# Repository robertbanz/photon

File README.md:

# Photon Game Platform

This is a software (and hardware) suite to run the Photon game system on reasonably modern hardware.

The software is known to run on FreeBSD, though there is nothing that would stop it from running cleanly on any modern Unix with the appropriate dependencies installed. While previous revisions involved some C modules, everything now is just raw Tcl/Tk.

TL;DR Check this out in /usr/photon, and you're good to go. (will get to the specifics later)

system_build/game contains some instructions that were used to build the "game computer" we have used at PhoCon. This consists of a Mac-based host (that runs the lighting control software natively), and two virtual machines. One that runs pfsense and acts as a router to the private network that runs the Photon bits, and a second VM that runs the game software.

## Hardware

Previous revisions of this software -- you can check back in the commit history -- were expected to run on PC hardware (a Pentium at the time) on FreeBSD 2.x. It used a kernel module that modified the low-level timer handling to match what the Photon player units (PODs) expect. (see the README in the photon_gamma repository for more of that story)

As PC environment has evolved, the ability to match the Photon timing requirements became difficult. As part of making sure the software could move on and work on platforms beyond that could be picked up at computer swap-meets, some hardware assistance was required. The first attempt was to use some Arduino hardware, but a bare Arduino was not capable of reliably matching the POD's timing. I developed what I called the "PhoBoard" (schematics and layout in Eagle format are under hardware/) that provides an accurate timing interrupt in addition to an RS232-level serial port to connect to the central radio, and a modulated IR output when using the game computer itself as the entry terminal for the PODs.

The firmware for the PhoBoard(tm) is located in src/platformio/radio_interface. It is expected to run on an Arduino DUE, and be connected to the game computer (or game computer VM) via its programming port.

## Software

There are four primary components to the software. You'll find a lot of support scripts sitting around in bin/ to manage them, but this is what's important.

*  *bin/main* - It's called main for a reason. Listens on some ports for the ET & Displays to talk to, talks to the central radio via the Arduino, plays the game soundtrack, and has some fun menus to play with.
*  *bin/et* - The entry terminal. Talks to "main" to control game state. Can either use the IR emitter that *main* controls via the Arduino, or, to something connected to a local serial port that can provide a modulated IR output.
*  *bin/{cg,pg}display* - These drive the "Current Game" display, or "Post Game" display. At PhoCon we've ran these on Intel ComputeSticks running Ubuntu. They just need to be able to connect to the game computer and database to do their thing. They get constant updates about the state of the game, and in the case of the current game display, information about player state changes from *main* as they happen.  These have an "-hd" argument that selects for the 1080p layout, vs the old NTSC resolution screen layouts. (at PhoCon, all the displays are "hd")
*  *database* - The PostgreSQL database handles all of the state. For example, when the ET stages a game, it writes the data there, and just tells *main* to "start game number x". Similarly, when the displays need information about the game (or previous game), they query the DB.

### Running It In Production

*  The scripts that drive the ET & displays run them in a loop that upon startup will try to 'rsync' the entire /usr/photon tree from the game computer so they're running the latest revision of code.

*  As we're typically running this in a VM, if you've set up the FreeBSD image as I have, it launches the X windows server in a virtual frame buffer that's available via a VNC connection.

*  It also sets up PulseAudio (dot dot dot Total Junk dot dot dot SO much latency. So bad) to serve up the default audio input as the "background music" for the game, which will be faded out when the game starts.

## Configuration

etc/game.conf and etc/game.conf.local specify site specific and machine specific (respectively) parameters for system functionality. For example, the game.conf.local will specify a serial tty for the ET's IR output, while game.conf.local on the game computer points to the IR on the PhoBoard. game.conf is synced during the 'rsync' mentioed above, but .local is excluded.

## Having Fun

### Game Modes

The game modes available are defined in the database table g_modes, and make reference to actual code in lib/modes which define how various game events are handled. All current game modes use 'standard' but twiddle various parameters, but it's possible to change all the behaviors you want.

### Game Soundtracks

Similar to the game modes, the soundtracks and their lengths, etc, are defined in the g_tracks database table.

### Display Defaults

In lib/, the \*.defaults files -- in X Resources format -- allow tweaking of various fonts and layout parameters. The cg_idle sub directories contain custom tasks to display in-beween games. Perfect for advertising.

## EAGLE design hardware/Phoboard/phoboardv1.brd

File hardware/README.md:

#Hardware Designs

## Phoboard

Arduino shield to interface with the old Photon radio. (Designed to work on an
Arduino Due, 3.3v). Used in conjunction with the game software and the firmware
in src/platformio/radio_interface.

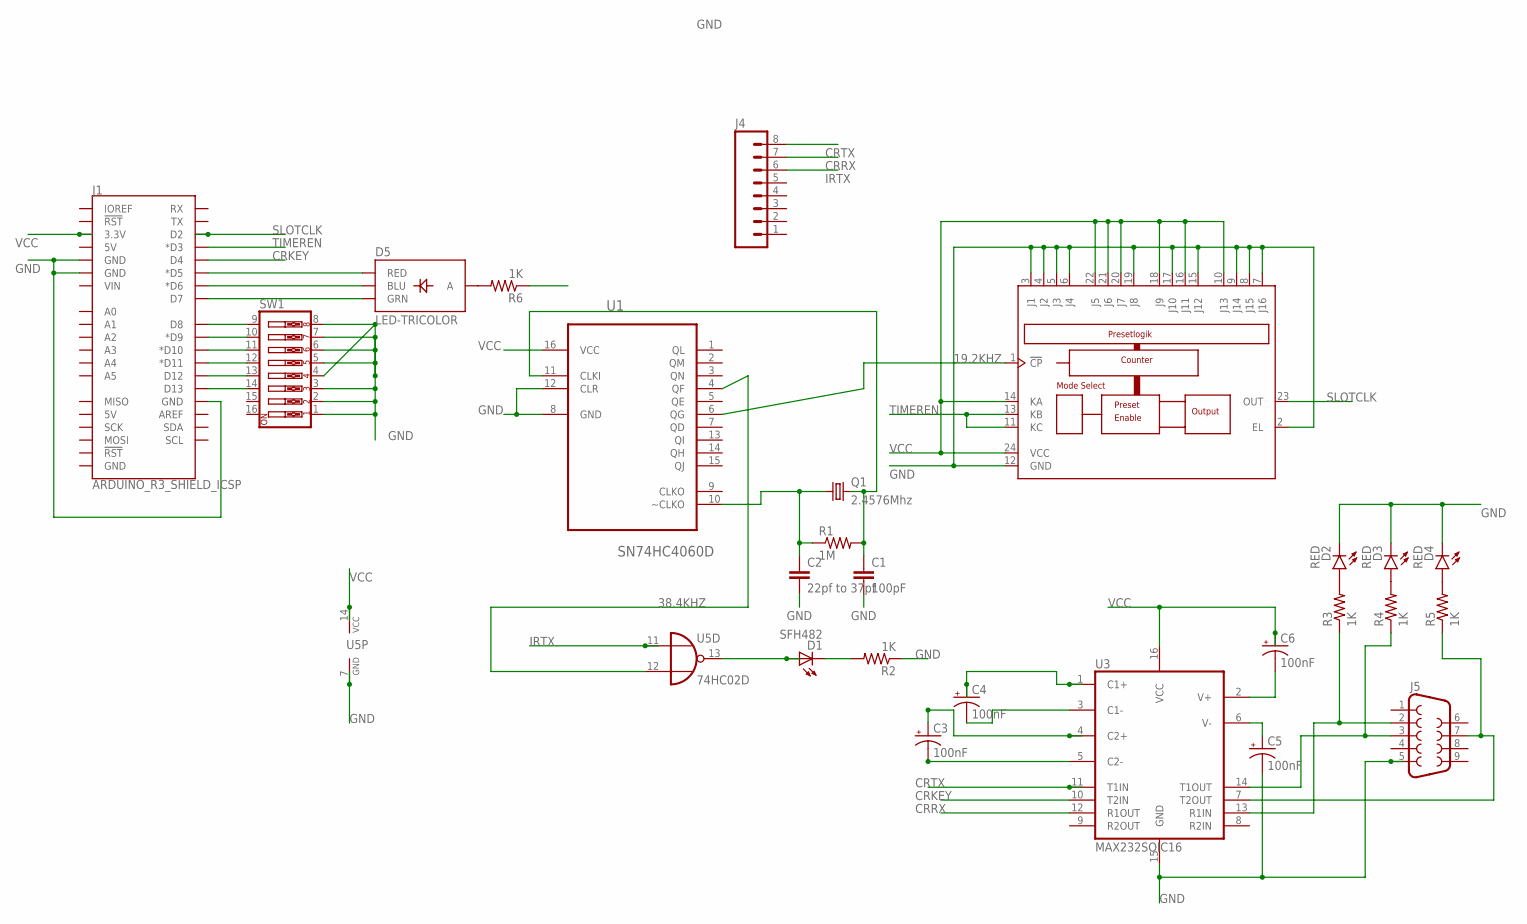
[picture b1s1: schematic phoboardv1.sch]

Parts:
C1: 100pF; CAP-PTH-SMALL-KIT
C2: 22pf to 37pf; CAP-PTH-SMALL-KIT
C3, C4, C5, C6: 100nF; EIA3216
D1: SFH482
D2, D3, D4: RED; LED-0603
D5: LED-TRICOLOR; LED-TRICOLOR-SMD
J1: ARDUINO_R3_SHIELD_ICSP; UNO_R3_SHIELD_ICSP
J4: M08; 1X08_ROUND
J5: DB9MALE; DB9_MALE
Q1: 2.4576Mhz; HC49U70
R1: 1M; AXIAL-0.4
R2, R3, R4, R5, R6: 1K; 0603-RES
SW1: SW_DIP-8; DIPSWITCH-08
U1: SN74HC4060D; SOIC127P600X175-16N
U2: 74HC59D; SO24W
U3: MAX232SOIC16; SO016
U5: 74HC02D; SO14

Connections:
19.2KHZ: U1.6 (QG), U2.1 (!CP)
38.4KHZ: U1.4 (QF), U5.12 (I1)
CRKEY: J1.D4, U3.10 (T2IN)
CRRX: J4.7, U3.12 (R1OUT)
CRTX: J4.8, U3.11 (T1IN)
D5: D5.R (RED), J1.D5 (*D5)
GND: C1.2, C2.2, C5.C (-), D2.C, D3.C, D4.C, J1.GND@0 (GND), J1.GND@1 (GND), J1.GND@2 (GND), J5.5, R2.1, R6.1, SW1.1, SW1.2, SW1.3, SW1.4, SW1.5, SW1.6, SW1.7, SW1.8, U1.8 (GND), U1.12 (CLR), U2.2 (EL), U2.3 (J1), U2.4 (J2), U2.5 (J3), U2.6 (J4), U2.7 (J16), U2.8 (J15), U2.9 (J14), U2.12 (GND), U2.15 (J12), U2.17 (J10), U2.19 (J8), U3.15 (GND), U5.7 (GND)
IRTX: J4.6, U5.11 (I0)
unnamed: C2.1, Q1.1, R1.P$1 (1), U1.10 (~CLKO)
unnamed: C1.1, Q1.2, R1.P$2 (2), U1.11 (CLKI)
unnamed: D1.A, U5.13 (O)
unnamed: D1.K (C), R2.2
unnamed: J5.2, R3.1, U3.13 (R1IN)
unnamed: J5.3, R4.1, U3.14 (T1OUT)
unnamed: J5.7, R5.1, U3.7 (T2OUT)
unnamed: C3.C (-), U3.5 (C2-)
unnamed: C3.A (+), U3.4 (C2+)
unnamed: C4.C (-), U3.3 (C1-)
unnamed: C4.A (+), U3.1 (C1+)
unnamed: D5.B (BLU), J1.D6 (*D6)
unnamed: C6.C (-), U3.2 (V+)
unnamed: C5.A (+), U3.6 (V-)
unnamed: D5.G (GRN), J1.D7
unnamed: J1.D8, SW1.9
unnamed: D2.A, R3.2
unnamed: D3.A, R4.2
unnamed: D4.A, R5.2
unnamed: D5.A, R6.2
unnamed: J1.D9 (*D9), SW1.10
unnamed: J1.D10 (*D10), SW1.11
unnamed: J1.D11 (*D11), SW1.12
unnamed: J1.D12, SW1.13
unnamed: J1.D13, SW1.14
SLOTCLK: J1.D2, U2.23 (OUT)
TIMEREN: J1.D3 (*D3), U2.11 (KC), U2.13 (KB)
VCC: C6.A (+), J1.3.3V, U1.16 (VCC), U2.10 (J13), U2.14 (KA), U2.16 (J11), U2.18 (J9), U2.20 (J7), U2.21 (J6), U2.22 (J5), U2.24 (VCC), U3.16 (VCC), U5.14 (VCC)

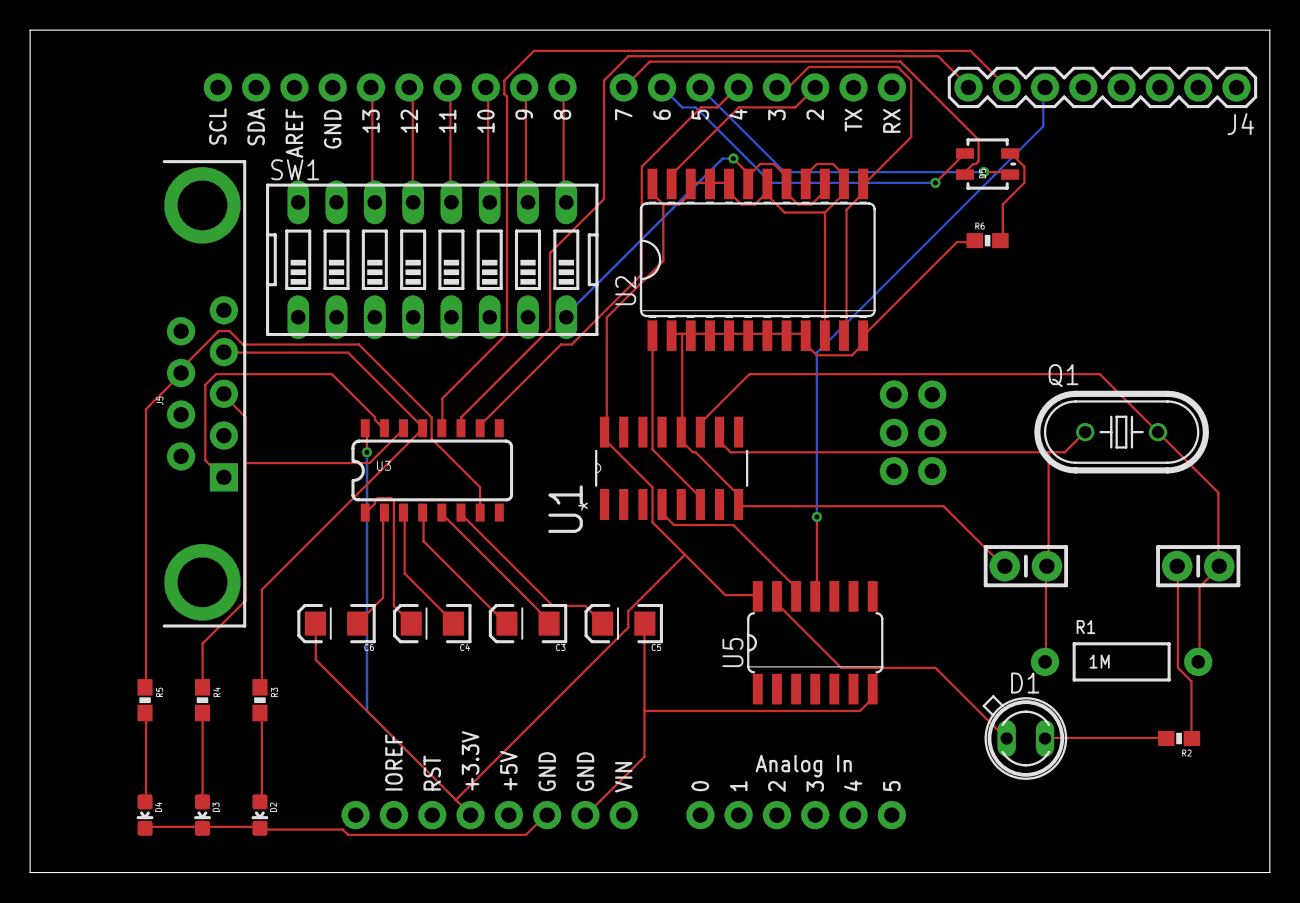
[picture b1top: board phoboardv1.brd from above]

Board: 2 copper layers, 82.2 x 55.9 mm, 26 parts (0 on the bottom side), 36 nets.

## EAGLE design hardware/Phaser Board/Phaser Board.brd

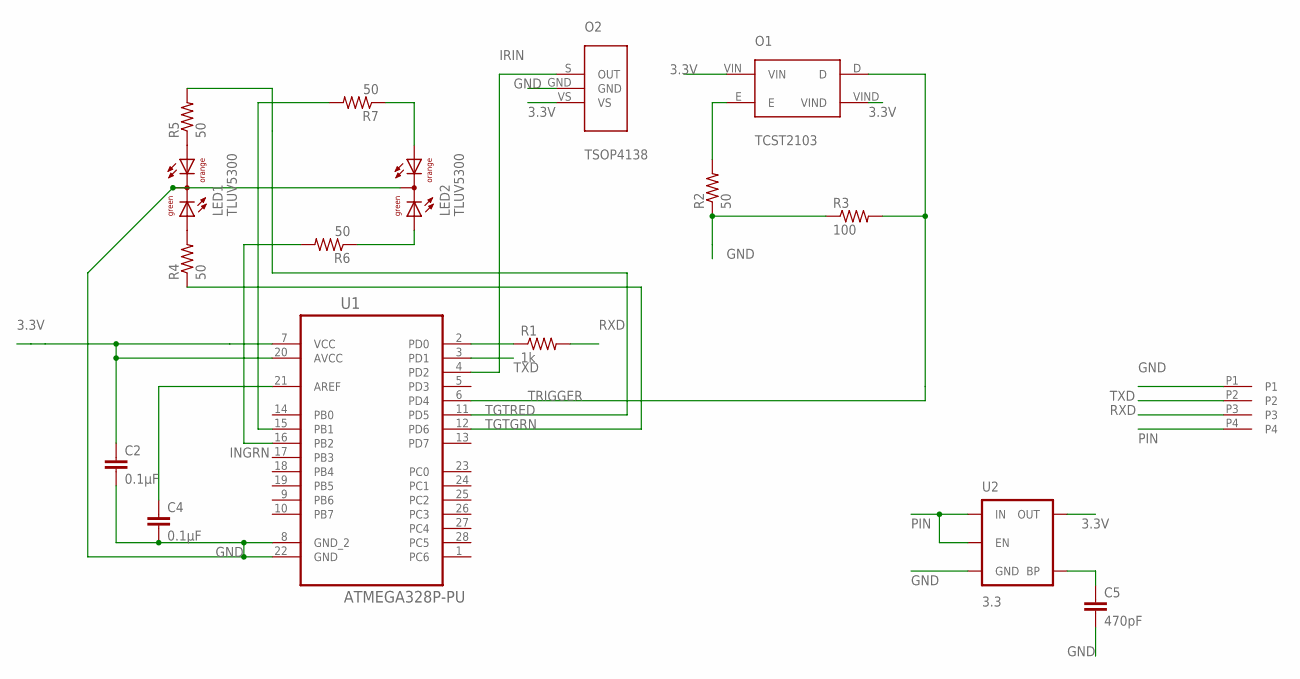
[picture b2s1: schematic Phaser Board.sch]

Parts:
C1: KK396-4
C2, C4: 0.1µF; 1206
C5: 470pF; 1206
LED1, LED2: TLUV5300
O1: TCST2103
O2: TSOP4138
R1: 1k; 0603-RES
R2, R4, R5, R6, R7: 50; 0603-RES
R3: 100; 0603-RES
U1: ATMEGA328P-PU; DIP254P762X457-28
U2: 3.3; SOT23-5

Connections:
3.3V: C2.1, O1.VIN, O1.VIND, O2.VS, U1.7 (VCC), U1.20 (AVCC), U2.5 (OUT)
GND: C1.P1, C2.2, C4.2, C5.2, LED1.CC, LED2.CC, O2.GND, R2.1, R3.1, U1.8 (GND_2), U1.22 (GND), U2.2 (GND)
INGRN: R6.2, U1.16 (PB2)
INRED: R7.2, U1.15 (PB1)
IRIN: O2.S (OUT), U1.4 (PD2)
unnamed: R1.1, U1.2 (PD0)
unnamed: C4.1, U1.21 (AREF)
unnamed: C5.1, U2.4 (BP)
unnamed: LED1.AG, R4.2
unnamed: O1.E, R2.2
unnamed: LED1.AO, R5.1
unnamed: LED2.AO, R7.1
unnamed: LED2.AG, R6.1
PIN: C1.P4, U2.1 (IN), U2.3 (EN)
RXD: C1.P3, R1.2
TGTGRN: R4.1, U1.12 (PD6)
TGTRED: R5.2, U1.11 (PD5)
TRIGGER: O1.D, R3.2, U1.6 (PD4)
TXD: C1.P2, U1.3 (PD1)

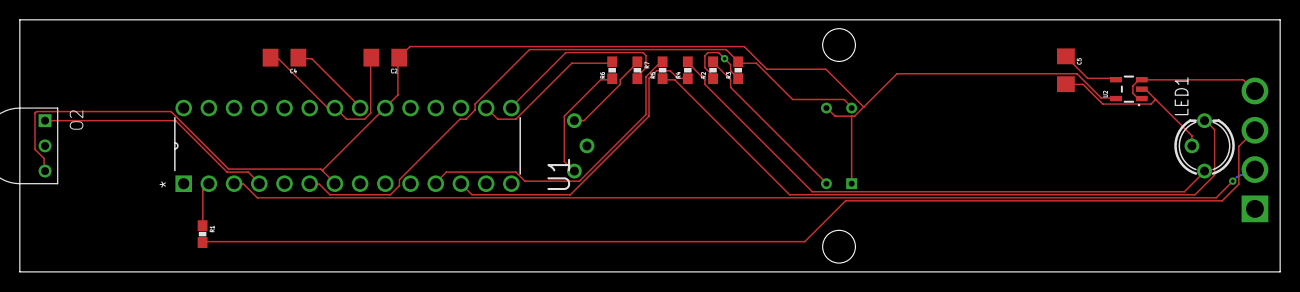
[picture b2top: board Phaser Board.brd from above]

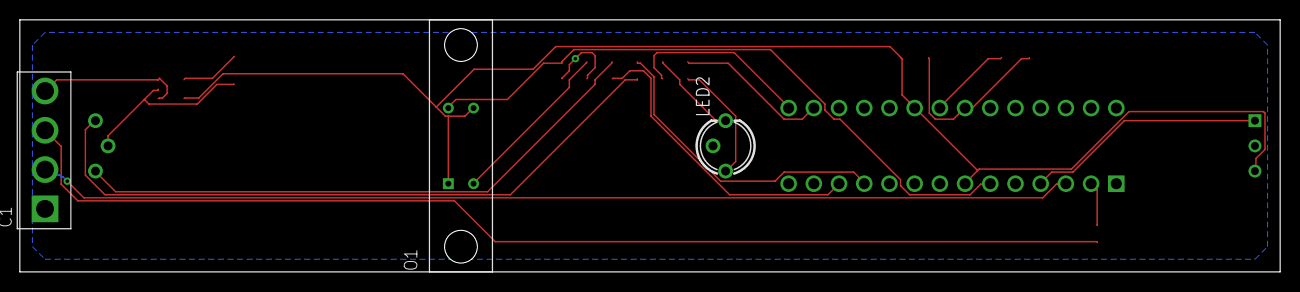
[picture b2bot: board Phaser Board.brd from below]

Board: 2 copper layers, 127.0 x 25.4 mm, 17 parts (3 on the bottom side), 19 nets.

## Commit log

2015-06-10 Import of mostly old stuff.
2015-06-10 2015 base updates.
2015-06-13 Add new VGA image assets w/ photon branding.
2015-06-13 Add Photon bug
2015-06-17 Game display cleanups
2015-06-17 Add soundtrack files.
2015-06-17 Rename defaults files.
2015-06-17 Add hd display defaults file.
2015-06-17 Add cr-over-net library
2015-06-18 working on hd display
2015-06-19 More display updates.
2015-06-19 HD images for game display
2015-06-20 Some display updates
2015-06-21 Update shebang lines to be more x-platform
2015-06-21 Helper scripts for remote displays
2015-06-22 More ET fixins.
2015-06-23 Almost there.
2015-06-23 net interface to the cr stuff.
2015-06-24 test video idle screens
2015-06-24 Re-arrange everything to match the installed dir layout
2015-06-24 More path-related fixups
2015-06-25 small updates for connection leaking and display
2015-06-25 video clip support in idle screen
2015-06-25 More display stuff coming together.
2015-06-25 More fixig of display sw.
2015-06-26 more work.
2015-06-26 Don't sync var anymore.
2015-06-27 small bug fixes
2015-06-28 true dat
2015-07-03 small fixes from testing, smoother mixer
2015-07-04 port connection fixes to pgdisplay
2015-07-04 Make the volume configurable
2015-07-08 Adjust fade times.
2015-08-25 version 1
2015-08-26 Persistent codename searches.
2015-08-29 production vixes
2015-12-27 update paths for running on server
2016-02-12 arduino cr interface initial commit
2016-02-18 basically working, still needs testing.
2016-03-08 add 74hc4059 lib
2016-03-08 work on timer
2016-04-10 Support for phoboard.
2016-04-12 Back in business.
2016-04-20 Better CR debug logs.
2016-04-23 Ditch the C for dealing with the ET/IR.
2016-05-06 fix radio offset for et
2016-06-08 Working radio interface board.
2016-06-18 Light control support.
2016-06-19 some more lighting stuff
2016-06-24 add tmp to ignore
2016-06-26 More of the lighting program.
2016-06-29 Add support for IR device on the radio interface.
2016-06-29 Add commands to support the IR emitter.
2016-07-04 lighting autostart script
2016-07-04 Start pulse during window manager startup, seems to work better.
2016-07-04 Add weights to the random track picker.
2016-07-04 Continued work on lighting programmies.
2016-07-09 Add the radio monitor back in.
2016-07-23 Updates to lighting, db handling, et socket hardening, et barcode scanner.
2016-07-23 Possibly final lighting program.
2016-07-23 TX queue management for radio (prevent queue overflows)
2016-07-24 Add new hd display feature (radio telemetry) and cleanups
2016-07-24 Be more agressive with not adding dups to the output queue.
2016-07-26 Updated deps
2016-07-26 remote parts of the remote display
2016-07-26 Script to run offsite display
2016-07-27 Keep offsite display alive
2016-07-27 Fix noidle mode
2016-07-27 Remove extra debugging.
2016-07-27 Logging timestamps & cleanups
2016-07-27 Initialize lastpollsn to avoid an unnecessary warning.
2016-07-27 Add real post game display to remote cgdisplay view.
2016-07-27 Remove noidle from remote display.
2016-07-30 trim the long window after 1k lines
2016-07-30 Add fog machine support.
2016-07-31 Few cleanups.
2016-08-05 Fix et enter pod binding.
2016-08-07 from phocon
2016-08-11 Add pc2016.
2016-08-14 Remove obsolete stuff.
2016-08-14 remove more obsolete stuff.
2017-04-14 add pod report script
2017-06-02 Handful of updates and changes.
2017-07-20 Changes from down under.
2017-07-29 Unfortunate Conflict of Evidence
2017-07-29 Version update.
2017-07-29 Remove old mixer code no longer in use.
2017-07-30 fix focus issues, autoload codename on scan
2017-07-30 fix background audio dropouts
2017-07-30 Updates to .xsession and add a .bashrc
2017-07-30 remove gratuitous grabs, and add a clear-game confirmation.
2017-08-03 Update audio fade-down timing.
2017-08-03 Make phaser stations really work.
2017-08-03 start pulsaudio before resetting hardware volumes
2017-08-03 bad channel 12 dimmer.
2018-07-26 Add some common libraries
2018-07-26 mor adds.
2018-07-26 add radio interface board hardware
2018-07-26 Added readme for hardware directory
2018-07-26 add filetype tags
2018-07-27 Moved radio_interface to platformio
2018-08-03 from-scratch system build data
2018-08-03 Updates to lighting startup script
2018-08-03 iterative progress on core hardware libs and phaser firmware
2018-08-03 make proto generation easier for nano & cpp in the same tree.
2018-08-04 Remap from failed channel 11 -> 15.
2018-08-05 Cleanup public repository
2018-08-05 Remove old central radio code
2019-05-13 don't check host keys in update script
2019-05-13 version tag
2019-09-07 some updates to the REAMDE.
2019-10-05 Remove bits that were dependent on nanoproto
2019-10-05 Add some documentation for the PhoBoard

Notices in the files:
parts and their libraries:
SparkFun-Passives: Licensing: Creative Commons ShareAlike 4.0 International - https://creativecommons.org/licenses/by-sa/4.0
